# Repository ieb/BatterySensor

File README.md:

# Battery Sensor

Aim is to create a low power smat shunt batter sensor reporting volage, current and temperatire over ModbusRTU.

Shunt is measured using a MAX9918 shut amplifier amplifying 48x a 75mV/100A shunt scaled down to 50mV to keep the MAX9918 input optimal.
Temperature by a 10K NTC read by ADC using an interpolation table.
Voltage by direct ADC with a voltage divder
RS485 by MAX485

# Protocol

Modbus RTU - bigendian

# Holding registers - function 3 to read, 6 to set

Stored in EEPROM, which is typically reset on a firmware upgrade.

| Offset | Name                          | type  | details                                          |
|--------|-------------------------------|-------|--------------------------------------------------|
| 0      | Device Adddress               | int16 | 1-254 modbus address, default is 2               |
| 1      | Voltage offset adjustment     | int16 | Offset in 0.1mv steps eg 10 = 1mV                |
| 2      | Voltage scale adjustment      | int16 | scale in 1/10000th eg 10000 = 1x                 |
| 3      | Current offset adjustment     | int16 | offset in 0.1mA steps eg 10 = 1mA                |
| 4      | Current scale adjustment      | int16 | scale in 1/10000th eg 10000 = 1x                 |
| 5      | Temperature offset adjustment | int16 | offset in C in 1/1000th eg 1000 = +1C            |
| 6      | Temperature scale adjustment  | int16 | scale in C in 1/1000th eg 1000 = 1x              |
| 7      | Serial Number                 | int16 | Device serial number, once set cannot be changed |

# Input Registers - function 4 to read

| Offset | Name            | type   | details                                 |
|--------|-----------------|--------|-----------------------------------------|
| 0      | Voltage         | int16  | Units 0.01V                             |
| 1      | Current         | int16  | Units 0.01A                             |
| 2      | Temperature     | int16  | 1 = 0.01C                               |
| 1001   | Recieved        | uint16 | count of frames recieved                |
| 1002   | Sent            | uint16 | count off frames send                   |
| 1003   | Errors Recieved | uint16 | count off frames recieved with errors   |
| 1004   | Ignored         | uint16 | count off frames dropped                |
| 1005   | Errors Sent     | uint16 | count off error frames send             |

# Other functions
* 17 - report - 4 bytes, uint8 device type (0x01), uint device on (0xff), int16 serial number (0xXXXX)

Exceptions are reported as per ModbuRTU Spec.

# MCU

Platform ATTiny8224
Could have also used a ATTiny84, but this has no uarts and requires ICSP programming.
Programmming using jtag2udpi on an Arduino Uno with avrdude.conf setup for the ATTiny8224, running at 5V.

# Voltage

The ATTiny ADC in 16bit using 4096 refrence through aa 32K/10K divider, gives withing 10mv of a 4 digit multi meter after calibration setting (0.9954 register 2 set to 9954). Hard to tell which is more accutage, probably the ADC. Voltage is stable with the LSB changing +- 1 or 2.

# Current

Multiple frustrating attempts with a current amplifier, eventually abandoned.

The originam MAX9918 had an unstable 75mV offset from the reference resistors at 0A which would not go, chip might have been damaged during soldering or the EP ground plane was not good enough.

2x INA169 that I had from years ago could not be made to amplify the input correctly at the required 47x gain. Looking back I had tried INA169 before and had problems eventually abandoning.

Now trying the Attiny3224 ADC + PGA at 16x which measures down to 0.0019mV perbit below 64mV differntial on the 16bit range with a 1024mV refrence, however this might really be 0.015625mV resolution as the 16 bit is oversampling 12bit. If it is, this represents a resolution of +-20mA which is perfectly reasonable for a 100A/75mV shunt. Quick testing indicates this is stable and repeatable with 10R on the input lines for protection from misconnection and 100nF accross the ADC inputs to remove high frequency components.

If that fails I will use one of the Alegro Hall chips, althought I prefer the simplicity of a shunt.

# debugging

Performed over serial on the second uart at 115200 baud.
Modbus is at 9600 baud 8N1

Building with DEVMODE (see main.cpp) defined allows the rs485 serial to be diverted to Serial1 and test patterns to be pasted from testpatterns.txt over the monitoring serial line.

Testing can be done with 

            pio run -e native 

which produces a native binary then

            cat testpattern.txt |  ./.pio/build/native/program

Which checks exercises the RS485 protocol using test patterns checking the response.

# Programming

Currently using jtag2udpi, via an Uno, but setting fuses seems hard
Needs a modified avrdude.conf file to add support for the attiny3224
pio run -t fuse -e attiny3224 does appear to work.

Fuses must be set to ensure the chip clock speed matches the compiled code. This only needs to be done once per chip.
It its not done the serial output doesnt sync with the baud rate and garbage is seen on the serial line.

    pio run -t fuses -e attiny3224

Looking at megaTinyCore support in the Arduino IDE using SerialUDPI is much better and more advanced.

    pio run -t upload -e attiny3224 

works ok for the moment.

# Board

For full details see the pcb/*
In outline.

            ------------------------------------------
            | a           1 2 3 4 5                 A|
            | b   MAX                      MAX      B|     
            | c   RS485   Atting3224       9918     C|     
            | d                                     D|     
            |     AMS1117                           E|
            ------------------------------------------     

            a = GND
            b = Vin (12v)
            c = RS485 A
            d = RS485 B

            1 = GND
            2 = +5V
            3 = UDPI
            4 = Debug RX
            5 = Debug TX

            A = Battery +Ve
            B = Shunt -
            C = Shunt +
            D = GND
            E = NTC

# Test client

in testclient/ requires python3.
install with 

    pip install -r requirements.txt

run with 

    python3 batterymon.py

# TODO

* [x] Check MAX9918 amplifier - Abandoned using MAX9918 as it had 75mV offset from its reference point and a lot of instability. Have switched to a pair of INA196 current amplifiers which so far draw much less current and seem stable
* [x] Test temperature
* [x] Test voltage
* [x] Test current - switched to direct to ADC which gives good 0mA stability, need to verify linearit
* [x] Test RS485 
* [x] Write Python Modbus RTU Controller to test for real.
* [ ] Calibrate
* [ ] Integrate with CanDiagnose controler to act as ModBus Controller for 1..n battery sensors.

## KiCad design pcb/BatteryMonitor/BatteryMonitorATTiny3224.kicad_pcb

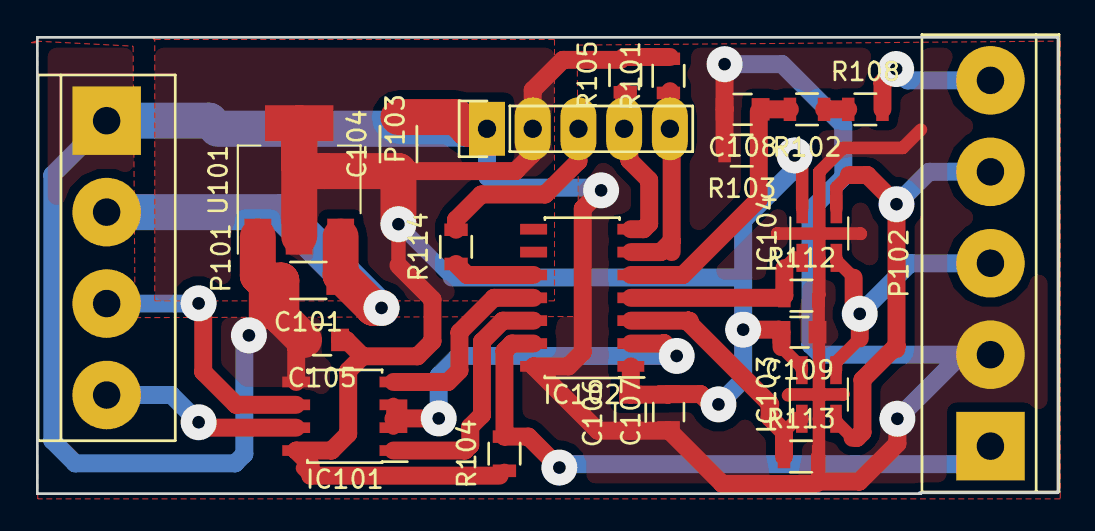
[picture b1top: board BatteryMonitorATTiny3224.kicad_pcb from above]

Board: 2 copper layers, 56.7 x 25.4 mm, 24 parts (0 on the bottom side), 20 nets.

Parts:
C101, C104: 10uF; C_1206
C105, C106, C109: 100nF; C_0805
C107: 1nF; C_0805
C108: C; C_0805
IC101: MAX3485E; SOIC-8_3.9x4.9mm_Pitch1.27mm
IC102: ATTINY3224-SS; SOIC-14_3.9x8.7mm_Pitch1.27mm
IC103, IC104: INA169; SOT-23-5_HandSoldering
P101: RS485; bornier4
P102: Bat; bornier5
P103: Prog; Pin_Header_Straight_1x05
R101, R103, R104, R105, R108: 10K; R_0805
R102: 22K; R_0805
R112, R113: 47K; R_0805
R114: 270R; R_0805
U101: AMS1117; SOT-223-3Lead_TabPin2

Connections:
5v: C104.1, C105.1, C106.2, C107.2, C109.2, IC101.8, IC102.1, IC103.5, IC104.5, P103.2, R101.2, R104.1, R105.2, U101.2
BatSenseV: C108.1, IC102.5, R102.2, R103.1
BatV+: P102.5, R108.2
CurSenseV: IC102.4, IC104.1, R112.1
GND: C101.2, C104.2, C105.2, C106.1, C107.1, C108.2, C109.1, IC101.5, IC102.14, IC103.2, IC104.2, P101.1, P102.2, P103.1, R103.2, R112.2, R113.2, U101.1
NTC: IC102.13, P102.1, R104.2
unnamed: IC102.10, R114.1
unnamed: R102.1, R108.1
RS485-A: IC101.6, P101.3
RS485-B: IC101.7, P101.4
RS+: IC103.4, IC104.3, P102.3
RS-: IC103.3, IC104.4, P102.4
RX: IC101.1, IC102.12
RXDebug: IC102.6, P103.5, R101.1
Sense-: IC102.3, IC103.1, R113.1
TX: IC101.4, IC102.11
TXDebug: IC102.7, P103.4, R105.1
TXEN: IC101.2, IC101.3, IC102.2
UDPI: P103.3, R114.2
Vin: C101.1, P101.2, U101.3

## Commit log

2022-06-15 Initial Commit, code and pcb implemented
2022-06-17 Working Board, tested over debug serial in DEVMODE
2022-06-17 Fixed doc
2022-06-23 Eliminated current Amp, using only Attiny3224 ADC
2022-06-25 Working over RS485 after blowing 1 chip and some timing issues
2022-06-26 Fixed and tested over modbus
2022-07-15 Added restart and diagnostics
